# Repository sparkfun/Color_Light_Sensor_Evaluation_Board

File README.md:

Color Light Sensor Evaluation Board
===================================

[  
*Color Light Sensor Evaluation Board (SEN-10701)*](https://www.sparkfun.com/products/10701)

This is an evaluation board for the ADJD-S311-CR999 color light sensor. 

Repository Contents
-------------------

* **/Firmware** - Example Arduino sketch to run the sensor board. 
* **/Hardware** - All Eagle design files (.brd, .sch)

License Information
-------------------
The hardware is released under [Creative Commons Share-alike 3.0](http://creativecommons.org/licenses/by-sa/3.0/).  
All other code is open source so please feel free to do anything you want with it; you buy me a beer if you use this and we meet someday ([Beerware license](http://en.wikipedia.org/wiki/Beerware)).

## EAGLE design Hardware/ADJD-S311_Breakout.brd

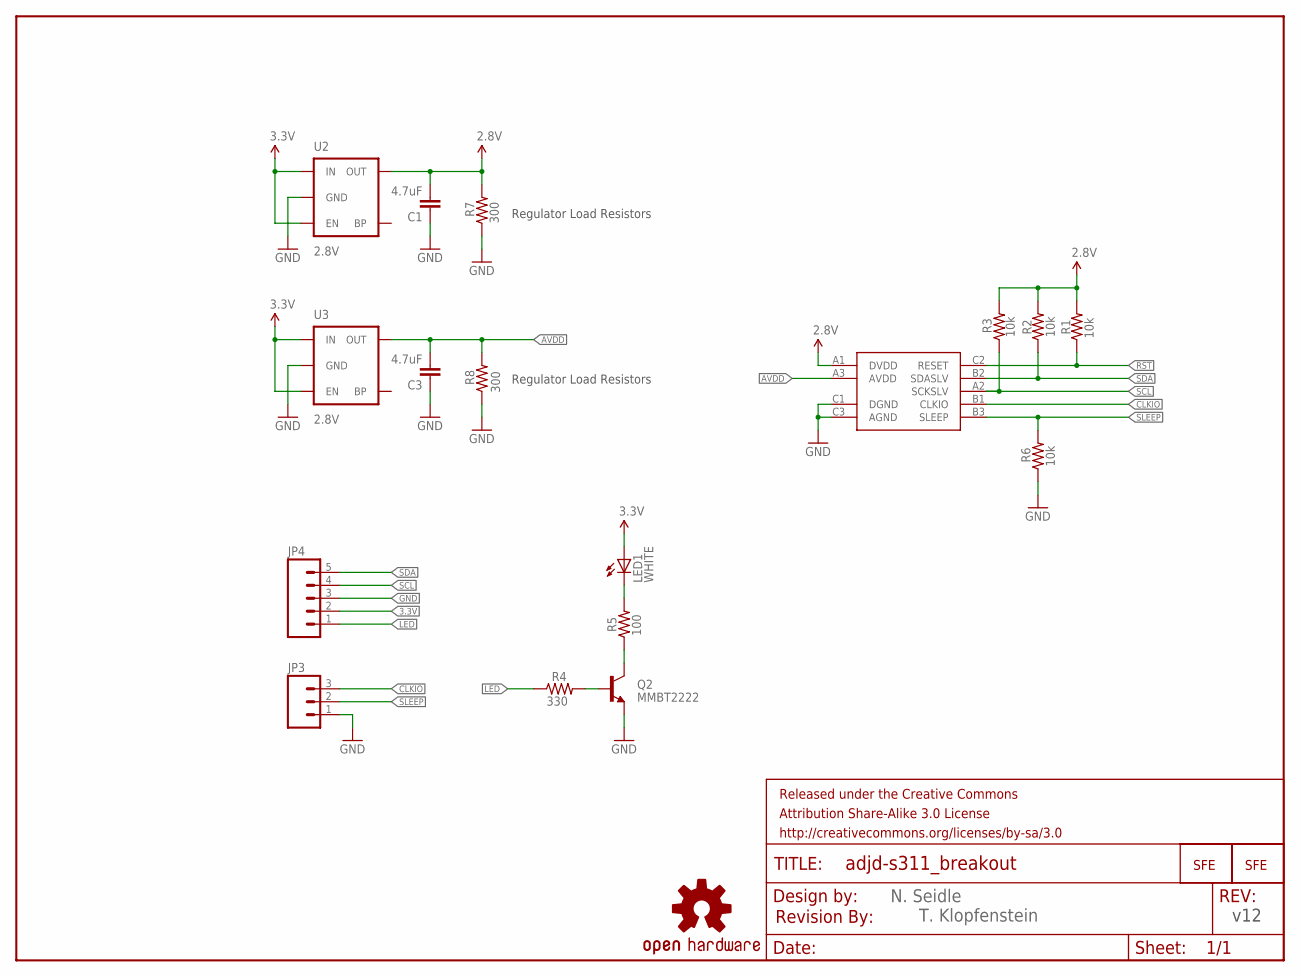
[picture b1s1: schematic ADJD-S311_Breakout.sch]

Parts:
C1, C3: 4.7uF; 0603-CAP
FRAME1: FRAME-LETTER; CREATIVE_COMMONS
JP1, JP2: LOGO-SFESK; SFE-LOGO-FLAME
JP3: M03PTH; 1X03
JP4: M05PTH; 1X05
LED1: WHITE; LED-0603
Q2: MMBT2222; SOT23-3
R1, R2, R3, R6: 10k; 0603-RES
R4: 330; 0603-RES
R5: 100; 0603-RES
R7, R8: 300; 0603-RES
U1: ADJD-S311-CR999; CSP-9
U2, U3: 2.8V; SOT23-5
U$1: REVISION
U$4: OSHW-LOGOS; OSHW-LOGO-S

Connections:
2.8V: C1.2, R1.2, R2.2, R3.2, R7.2, U1.A1 (DVDD), U2.5 (OUT)
3.3V: JP4.2, LED1.A, U2.1 (IN), U2.3 (EN), U3.1 (IN), U3.3 (EN)
AVDD: C3.2, R8.2, U1.A3 (AVDD), U3.5 (OUT)
CLKIO: JP3.3, U1.B1 (CLKIO)
GND: C1.1, C3.1, JP3.1, JP4.3, Q2.2 (E), R6.1, R7.1, R8.1, U1.C1 (DGND), U1.C3 (AGND), U2.2 (GND), U3.2 (GND)
LED: JP4.1, R4.1
unnamed: LED1.C, R5.2
unnamed: Q2.3 (C), R5.1
unnamed: Q2.1 (B), R4.2
RST: R1.1, U1.C2 (RESET)
SCL: JP4.4, R3.1, U1.A2 (SCKSLV)
SDA: JP4.5, R2.1, U1.B2 (SDASLV)
SLEEP: JP3.2, R6.2, U1.B3 (SLEEP)

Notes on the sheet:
Regulator Load Resistors
N. Seidle
v12
T. Klopfenstein

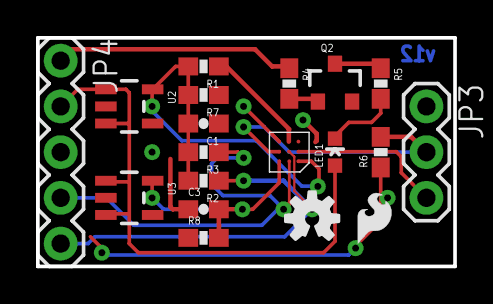
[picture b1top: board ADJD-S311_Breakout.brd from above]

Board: 2 copper layers, 23.2 x 12.7 mm, 22 parts (1 on the bottom side), 13 nets.

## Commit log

2013-07-12 Updated board files for v12
2013-07-29 Fixed footprint to testing
2013-12-11 Revering to v10 hardware files as IC is EOL and revision will not be occuring
2025-06-27 Update README.md
    Updating link

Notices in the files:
parts and their libraries:
SparkFun-Aesthetics: Licensing: CC v3.0 Share-Alike You are welcome to use this library for commercial purposes.
SparkFun-Aesthetics: Released under the Creative Commons Attribution Share-Alike 3.0 License
SparkFun-Aesthetics: Released under the Creative Commons
